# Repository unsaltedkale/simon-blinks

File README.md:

# simon-blinks

This is a PCB board that I made for [🗺️ Pathfinder](https://pathfinder.hackclub.com/)! It's made to play a five-color version of Simon Says.

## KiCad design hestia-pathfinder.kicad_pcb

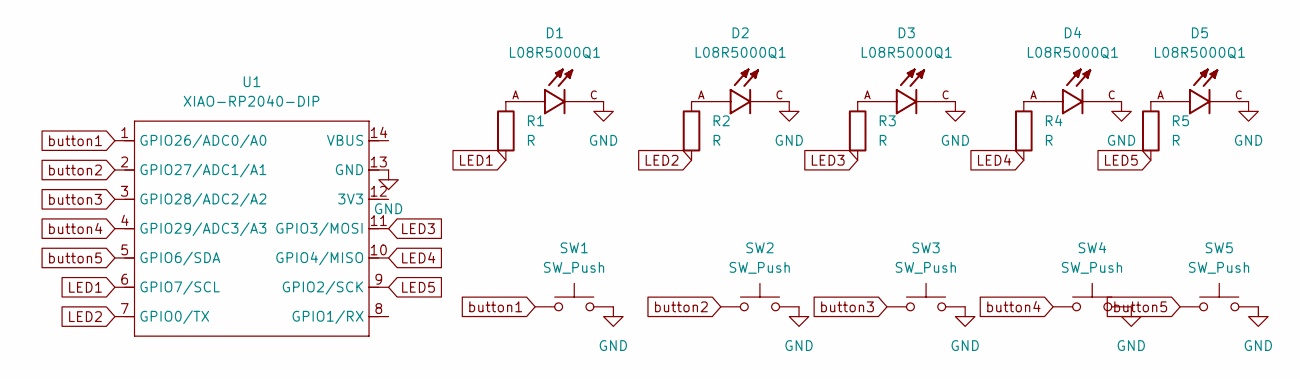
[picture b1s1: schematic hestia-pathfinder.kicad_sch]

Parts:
D1, D2, D3, D4, D5: L08R5000Q1; LEDRD254W57D500H1070; PARTREV NA
R1, R2, R3, R4, R5: R; R_Axial_DIN0204_L3.6mm_D1.6mm_P5.08mm_Horizontal
SW1, SW2, SW3, SW4, SW5: SW_Push; SW_Cherry_MX_1.00u_PCB
U1: XIAO-RP2040-DIP

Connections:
GND: D1.C, D2.C, D3.C, D4.C, D5.C, SW1.2, SW2.2, SW3.2, SW4.2, SW5.2, U1.13 (GND)
LED1: R1.2, U1.6 (GPIO7/SCL)
LED2: R2.2, U1.7 (GPIO0/TX)
LED3: R3.2, U1.11 (GPIO3/MOSI)
LED4: R4.2, U1.10 (GPIO4/MISO)
LED5: R5.2, U1.9 (GPIO2/SCK)
unnamed: D1.A, R1.1
unnamed: D2.A, R2.1
unnamed: D3.A, R3.1
unnamed: D4.A, R4.1
unnamed: D5.A, R5.1
button1: SW1.1, U1.1 (GPIO26/ADC0/A0)
button2: SW2.1, U1.2 (GPIO27/ADC1/A1)
button3: SW3.1, U1.3 (GPIO28/ADC2/A2)
button4: SW4.1, U1.4 (GPIO29/ADC3/A3)
button5: SW5.1, U1.5 (GPIO6/SDA)

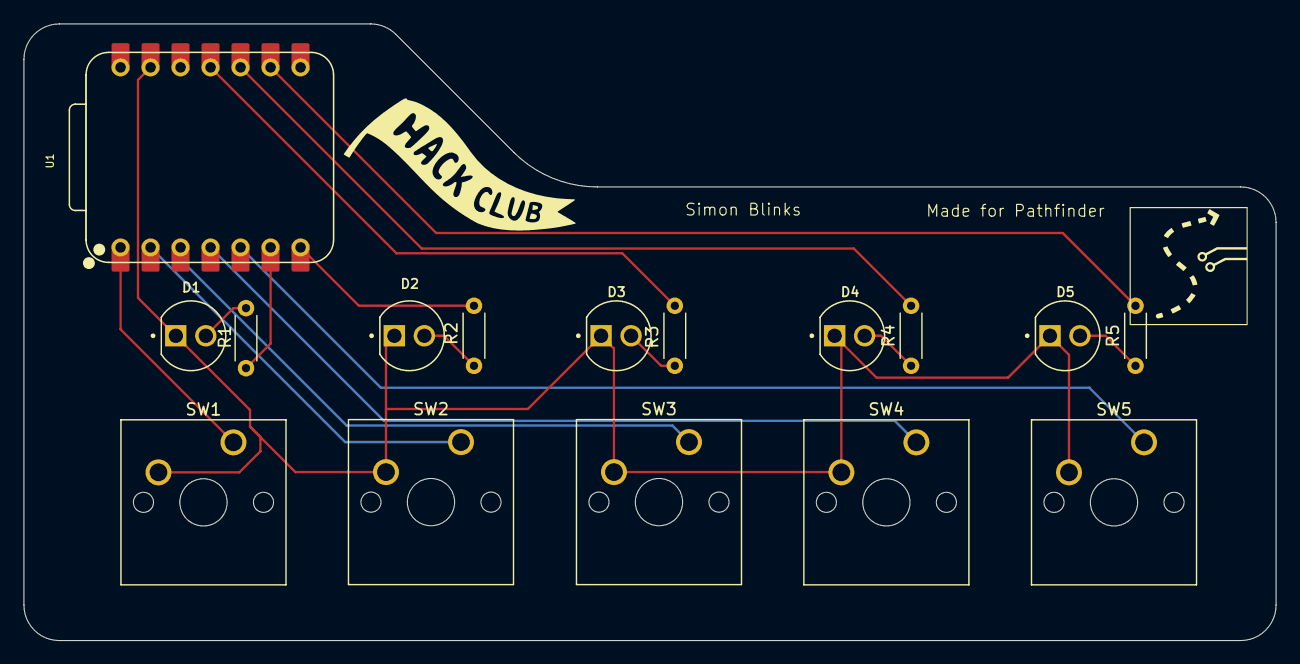
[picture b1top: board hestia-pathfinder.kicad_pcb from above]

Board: 2 copper layers, 106.0 x 52.2 mm, 16 parts (0 on the bottom side), 16 nets.

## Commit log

2025-07-03 adding all my pcb progress
